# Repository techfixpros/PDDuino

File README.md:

# PDDuino
A [Tandy Portable Disk Drive](http://tandy.wiki/TPDD) emultaor implemented on Arduino, using a micro-sd card for storage.

<!-- old gmail acct

-->

<!--
Earlier stages:<br>

-->

PDDuino was based originally on [SD2TPDD](https://github.com/tangentdelta/SD2TPDD) by Jimmy Petit.  

DISCLAIMER: This is not a great reference for a TPDD server yet. [dl2](https://github.com/bkw777/dl2) is.  
[pdd.sh](https://github.com/bkw777/pdd.sh) is a good reference for a TPDD _client_, though not especially easy to follow the bash code since it is written to conform to a purist standard as a stunt more than to be easy to read and follow.  
The next major TODO is to rewrite this using dl2 as the reference.

## Features
* Tandy Portable Disk Drive 1 emulation
* TS-DOS directories<br>
* TPDD2-style bootstrapper to install a [TPDD Client](http://tandy.wiki/TPDD_client) onto the computer<br>

## Hardware support
PDDuino runs on most any Arduino-compatible microcontroller.  

Configs are already included to support the following particularly handy development boards that have a small form factor, built-in usb power & console, and built-in SD-card reader, and which are supported by [MounT](https://github.com/bkw777/MounT) and [BCR_Breakout](https://github.com/bkw777/BCR_Breakout) for the serial connection, power, and physical attachment to the computer.  
 * Teensy [3.5](https://www.pjrc.com/store/teensy35.html) and [3.6](https://www.pjrc.com/store/teensy36.html)  ([4.1](https://www.pjrc.com/store/teensy41.html) pending)  
 * Adafruit [Feather 32u4 Adalogger](https://www.adafruit.com/product/2795)(most recommended) and [Feather M0 Adalogger](https://www.adafruit.com/product/2796)

PDDuino may be used with any machine that has [TPDD client](http://tandy.wiki/TPDD_client) software or firmware.  
 * TRS-80/TANDY Models 100, 102, 200, WP-2  
 * NEC PC-8201, PC-8201A, PC-8300, PC-8401A, PC-8500  
 * Olivetti M10  
 * Kyotronic KC-85  
 * [Cambridge Z88](http://www.rakewell.com/xob/xob.shtml)  
 * [Brother knitting machines](http://www.k2g2.org/wiki:brother_fb-100)  
 * [Anything with a python interpreter](https://trs80stuff.net/tpdd/)  
 * [pdd.sh](https://github.com/bkw777/pdd.sh)  

## Requirements / Setup
### Software
[Arduino IDE Setup](Arduino_IDE_Setup.txt)

### Hardware
* Arduino-compatible microcontroller board with at least one hardware serial port
* SD card reader
* RS-232 to TTL/CMOS level shifter
* Serial cable
* Battery or usb power source for the microcontroller board

These boards have a small form-factor, and sd-card reader built-in:  
  [Adafruit Feather 32u4 Adalogger](https://learn.adafruit.com/adafruit-feather-32u4-adalogger) (best choice)<br>
  [Adafruit Feather M0 Adalogger](https://learn.adafruit.com/adafruit-feather-m0-adalogger) (20200916 broken)<br>
  [Teensy 3.5](https://www.pjrc.com/store/teensy35.html)<br>
  [Teensy 3.6](https://www.pjrc.com/store/teensy36.html)<br>
  [Teensy 4.1](https://www.pjrc.com/store/teensy41.html) (not yet tested)

  The ideal is the Alalogger 32u4, even though it's old and you can get far more powerful boards for the same or less cost, and you may have to get it from a reseller like Digikey or Mouser, the Adalogger 32u4 is really the optimal choice for several reasons, at least until the glitch with the M0 version is worked out, or one of the new Huzzah boards are supported.

  The Teensy's work well in all the impoprtant ways, but they have symmetrical pin headers so they can be plugged in backwards, don't have battery connectors or chargers, or card-detect switches on the card slots. The extra led next to the card slot on the Adafruit boards is nice for a disk activity light too. But without wifi and with the ability to underclock down to nothing, they draw low enough power that the lack of battery is offset by the fact that it can be powered from the BCR port without destabilizing the computer.

This adapter takes the place of a serial cable, and includes the level-shifter:<br>
  [MounT](https://github.com/bkw777/MounT)

This adapter can power the microcontroller board from the M100:<br>
  [BCR-USB-Power adapter](http://www.github.com/bkw777/BCR_Breakout)

**The following below are NOT needed if using the MounT adapter.  
You would only need these for bread-boarding or building in a box attached by a cable.**

 RS-232&lt;--&gt;TTL/CMOS level-shifter module:  
  [NulSom](https://www.amazon.com/dp/B00OPU2QJ4/)  
  Has a male connector and DTE pinout like a PC  
  Use the same special null-modem cable as for connecting a "Model T" to a PC.  
  Solder jumper wires on the back of the 9-pin connector to join pins 1, 4, and 6  
  [DSR-DTR-DCD Wiring, top](https://photos.app.goo.gl/oBpAbAbCgE8yCJzm7)  
  [DSR-DTR-DCD Wiring, bottom](https://photos.app.goo.gl/mj1SXce5fJnmZiyr6)  
  This short-circuits the DSR/DTR detection, which pacifies TS-DOS so it will run, but means you can't test the bootstrap function except by wiring up a fake DTR/DSR signal using a pulldown resistor to gnd and a momentary button to vcc/3v3 on gpio pin 6.  

 RS-232 cable:  
  [PCCables 0103](https://www.pccables.com/products/00103.html)  
  Or [Any of these](http://tandy.wiki/Model_T_Serial_Cable)

 TODO: find a ttl-serial module that actually supports the dsr/dtr lines.  
  https://www.pololu.com/product/126   breadboard-friendly single row of pins  
  https://www.amazon.com/dp/B0190WSINY/  double row pin header needs jumper wires to a breadboard  
  Female plug, DCE pinout, needs a different serial cable, or adapters.

## Usage:
### Normal usage
Use as you would use a real [TPDD](http://tandy.wiki/TPDD) or any other [TPDD emulator](http://tandy.wiki/TPDD_Emulators).

### Bootstrap Procedure
Assuming you are using a [MounT](https://github.com/bkw777/MounT) adapter to host a Feather or Teensy.  
Assuming you are using the [BCR-USB](https://github.com/bkw777/BCR_Breakout) adapter to power the MounT.  
Assuming the portable is a Model 100.  
Assuming you want to install TS-DOS.  

1. Start with the Model 100 turned off.  
 Plug the MounT and BCR adapters into the Model 100 and connect the usb cable from the BCR adapter to the MounT.  
 Eject the SD card.

1. Place an ascii format BASIC loader file on the root of the SD card, renamed as LOADER.DO.  
You can use any of the loader files from [dlplus](https://github.com/bkw777/dlplus/tree/master/clients).  
&nbsp;  
Example 1: To install TS-DOS on a TRS-80 Model 100: Take [TS-DOS.100](https://raw.githubusercontent.com/bkw777/dlplus/master/clients/ts-dos/TS-DOS.100), and save it as ```LOADER.DO``` on the root of the SD card.  
Note the associated [pre-install](https://raw.githubusercontent.com/bkw777/dlplus/master/clients/ts-dos/TS-DOS.100.pre-install.txt) and [post-install](https://raw.githubusercontent.com/bkw777/dlplus/master/clients/ts-dos/TS-DOS.100.post-install.txt) directions.  
&nbsp;  
Example 2: To install DSKMGR on an Olivetti M10: Take [DSKMGR.M10](https://raw.githubusercontent.com/bkw777/dlplus/master/clients/dskmgr/DSKMGR.M10), and save it as ```LOADER.DO``` on the root of the SD card.  
Note the associated [pre-install](https://raw.githubusercontent.com/bkw777/dlplus/master/clients/dskmgr/DSKMGR.M10.pre-install.txt) and [post-install](https://raw.githubusercontent.com/bkw777/dlplus/master/clients/dskmgr/DSKMGR.M10.post-install.txt) directions.  

1. Turn on the Model 100 while the SD card is still ejected.  
The Arduino board should now have a steady slow blinking LED, indicating it's waiting for an SD card.  
Don't insert the SD card yet.

1. In BASIC, type ```RUN "COM:98N1E"``` and press Enter.  
(Or follow the pre-install directions are for the loader you're using. The exact command is different for different models of computer. This example is for TRS-80 Model 100 or 102.)

1. Insert the SD card.

1. Wait while the loader program is transferred and then executed.  
For approximately 20 seconds (exact time depends on the size of LOADER.DO) there will be no indication of acivity on the computer, and the LED on the Arduino board will be ON solid and not blinking. The loader program is being sent to the computer during this time.  
&nbsp;  
After the LED goes out, the computer executes the program that was just loaded.  
&nbsp;  
Follow any on-screen directions (different loaders have different prompts & directions), and the post-install directions for the loader you're using.  
In the case if TS-DOS, this would be:  
&nbsp;&nbsp;Type ```SAVE "TS-DOS"``` and press Enter.  
&nbsp;&nbsp;Exit BASIC (press ```F8``` or type ```MENU```)  
&nbsp;&nbsp;Run ```TS-DOS.BA``` from the main menu.  
&nbsp;&nbsp;Use ```F2-Kill``` to delete ```TMP.DO```  

You now have the ram version of TS-DOS (or other tpdd client) installed.  
You can immediately use it to browse the contents of the SD card.

## Notes
### Ultimate ROM II TS-DOS loader
If you plan on using Ultimate Rom II, it has a "TS-DOS" feature which works by loading TS-DOS into ram on the fly, from a file on disk.  
The file must be named DOS100.CO, and be in the root directory of the media.  
This file can be downloaded from <http://www.club100.org/nads/dos100.co>, or,  
a modified/updated version can be found here: <http://www.club100.org/memfiles/index.php?direction=0&order=&directory=Ken%20Pettit/NewDos>

### "Model T" serial port control lines
At power-on the Model 100 rs232 port sets all data & control pins to -5v.  
On RUN "COM:98N1E", pins 4 and 20 go to +5v.  

## To-Dos, or merely ideas, not necessarily realistic
* Change "PARENT.<>" to "..<>" if possible
* https://www.arduinolibraries.info/libraries/double-reset-detector_generic
* https://github.com/rocketscream/Low-Power  
  simplify the sleep calls, same lib for both avr and samd21  
* RTC (Teensy has built-in rtc)
* play & record audio as virtual cassette (Teensy has built-in audio, and enough cpu & ram to use it)
* Battery level (Adalogger has built-in voltage reference and adc, and a built-in lipo charger)
* A command-line that can be accessed from the computer's terminal emulator for quicker file manipulation
* Hayes modem emulation using an ESP8266 (<https://www.cbmstuff.com/proddetail.php?prod=WiModem232>)
* FTP server/client access using an ESP8266

## BUGS/STATUS
* 20200916 Feather M0 isn't working.  
  Unknown why. It used to work.

* Works with TS-DOS.

* Doesn't work with TEENY. (hangs)

* File transfers don't work with TpddTool.py .  
Seems to be due to mis-matches in handling the space-padding in the filenames?  
Problem may be at least partly in TpddTool.py

* Some kind of working directory initial/default state issue, which affects Ultimate Rom II loading DOS100.CO on the fly.
If you have DOS100.CO in ram, then UR-2 works all the time, because it will use that copy if available.  
TS-DOS from rom or ram, not via UR-2, seems to be working pretty well all the time.  
TS-DOS from rom or ram, not via UR-2, can successfully load a file like DOS100.CO from the root dir, but Ultimate Rom 2 usually can not load that same file, but sometimes it can.  
If you try to use TS-DOS from UR2 after a fresh power-cycle of both Arduino and M100, It doesn't work.  
But If you load TS-DOS some other way (for example, use a REX to switch to TS-DOS rom), and use TS-DOS to read the directory listing once, then switch roms back to UR-2, THEN the TS-DOS menu entry in UR-2 works (successfully loads DOS100.CO from the disk).  
Maybe TS-DOS does some kind of initialization that UR-2 isn't doing?  
UR-2 works fine with a real TPDD/TPDD2 and other emulators like dlplus and LaddieAlpha, so maybe there is some sort of default condition that we should be resetting to?  

* If you use UR-2 to load TS-DOS in ram, and switch to a subdirectory like /Games while in TS-DOS, then exit TS-DOS, then you can't use TS-DOS any more, because the next time UR-2 tries to load DOS100.CO from disk, SD2TPDD looks for /Games/DOS100.CO, which does not exist.

* When UR-2 loads DOS100.CO, sucessfully or not, the LED doesn't shut off after.

* Sometimes displays the "PARENT.<>" directory entry even when you are already in the root dir.  
Goes away if you try to open PARENT.<> again when you're already in root.

## Change-log

### 20210404
* 0.5.0 Incorporated Jim Brain's replacement return_*() and main loop.

### 20200819
* Moved PCB to its own [repo](https://github.com/bkw777/MounT)  
* Added TPDD2-style bootstrap function  

### 20200817
* Added PCB adapter "PDDuino_Feather".  
 Takes the place of the serial cable and ttl-rs232 module.  
 Supports Adafruit Feather 32u4 Adalogger and Adafruit Feather M0 Adalogger.  

### 20191025
* Support Adafruit Feather M0 Adalogger  
 needs "compiler.cpp.extra_flags=-fpermissive" in ~/.arduino15/packages/adafruit/hardware/samd/1.5.4/platform.local.txt
* Combine all boards supported into the same code  
 Time to break this out into a config.h file?

### 20180921
* Support Teensy 3.5/3.6
* Support Adafruit Feather 32u4 Adalogger
* Macro-ify all serial port access, debug and tpdd client
* sleepNow() powersaving, idles at 3ma
* dmeLabel[] & setLabel() TS-DOS shows current working dir in top-right corner
* disk-activity led

### SD2TPDD - PDDuino

### v0.2 (7/27/2018)
* Added DME support
* Corrected some file name padding bugs

### v0.1 (7/21/2018)
* Initial testing release with basic TPDD1 emulation

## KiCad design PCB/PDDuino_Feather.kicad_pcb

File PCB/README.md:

# PDDuino PCBs

## PDDuino_Feather - for Adafruit Feather Adalogger, 32u4 and M0

Get the PCB from OSHPark: <https://oshpark.com/shared_projects/0NVCii0o><br>
Get the parts from Digi-Key: <https://www.digikey.com/short/zr423m><br>

The Digi-Key cart is a complete BOM, including Feather 32u4 Adalogger board, 105mah lipo battery, and pin header sockets.<br>

You may want to remove any/all the following from the cart:<br>
* Battery - If you use the BCR port or other usb power source, then you don't need the battery.<br>
* Socket headers - If you want to solder the Adalogger board, then you don't need the sockets.<br>
* Adalogger board - If you already have one, you don't necessarily need more.

The same PDDuino_Feather adapter board works for both the 32u4 and the M0 versions of Adalogger boards.

## PDDuino_Teensy35 - for Teensy 3.5
coming

## PDDuino_Teensy36 - for Teensy 3.6
coming

## PDDuino_Teensy41 - for Teensy 4.1
coming

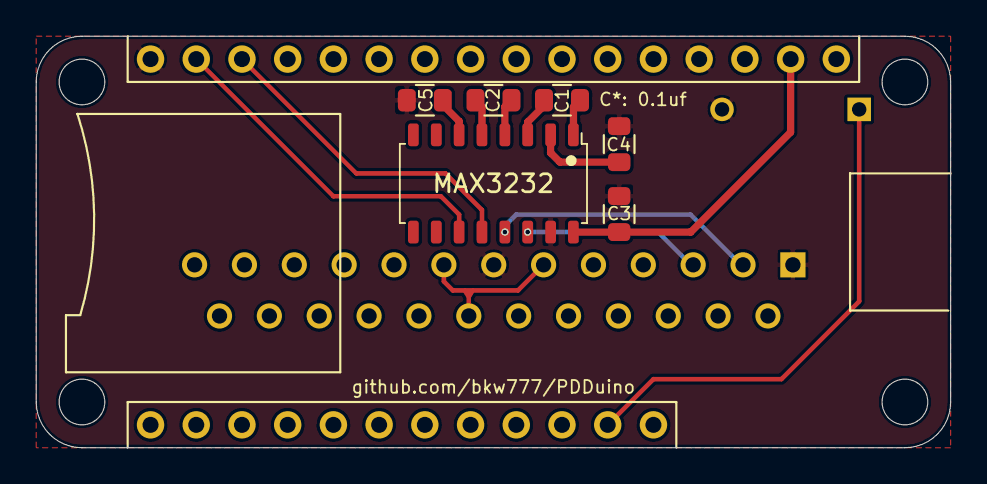
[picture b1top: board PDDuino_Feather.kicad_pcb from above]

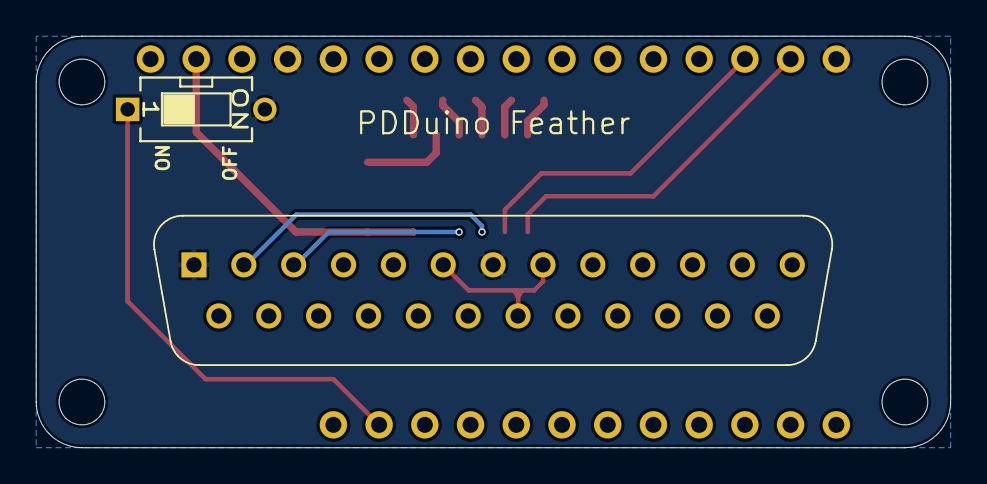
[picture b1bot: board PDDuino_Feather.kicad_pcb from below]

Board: 2 copper layers, 50.8 x 22.9 mm, 10 parts (2 on the bottom side), 16 nets.

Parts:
C1, C2, C3, C4, C5: 0.1uf; C_0805
J1: Adafruit_Feather_Adalogger
J2: DB25_Male; DSUB-25_Male_Vertical_P2.77x2.84mm
NT1: Net-Tie_3_Tee; NetTie-3_SMD_10_tri
S1: DS04-254-1L-01BK; SW_DS04-254-1L-01BK
U1: MAX3232; SOIC-16_W3.90mm

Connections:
/3V3: C3.1, J1.2, U1.16
/DCD: J2.8, NT1.1
/DSR: J2.6, NT1.3
/DTR: J2.20, NT1.2
/En: J1.27, S1.1A
/RXD: J2.3, U1.14
/RXD_TTL: J1.14, U1.12
/TXD: J2.2, U1.13
/TXD_TTL: J1.15, U1.11
GND: C3.2, C4.2, C5.2, J1.4, J1.16, J2.1, J2.7, S1.1B, U1.15
unnamed: C1.1, U1.1
unnamed: C1.2, U1.3
unnamed: C2.1, U1.4
unnamed: C2.2, U1.5
unnamed: C4.1, U1.2
unnamed: C5.1, U1.6

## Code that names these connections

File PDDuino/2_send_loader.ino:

#if defined(LOADER_FILE)
/*
 * sendLoader() and restart()
 *
 * At power-on the Model 100 rs232 port sets all data & control pins to -5v.
 * On RUN "COM:98N1E", pins 4 (RTS) and 20 (DTR) go to +5v.
 * github.com/bkw777/MounT connects GPIO pin 5 through MAX3232 to RS232 DSR (DB25 pin 6) and to RS232 DCD (DB25 pin 8)
 * and connects RS232 DTR (DB25 pin 20) through MAX3232 to GPIO pin 6.
 * To assert DTR (to RS232 DSR), raise or lower GPIO pin 5.
 * To read DSR (from RS232 DTR), read GPIO pin 6.
 */

/* TPDD2-style bootstrap */
void sendLoader() {
  byte b = 0x00;
#if DEBUG
  int c = 0;
#endif // DEBUG
  File f = SD.open(LOADER_FILE);

  DEBUG_PRINTL(F("sendLoader()"));  
  if (f) {
    SD_LED_ON
    DEBUG_PRINT(F("Sending " LOADER_FILE " "));
      while (f.available()) {
        b = f.read();
        CLIENT.write(b);
#if DEBUG
        if(++c>99) {
         DEBUG_PRINT(F("."));
         c = 0;
        }
#endif // DEBUG
        delay(LOADER_MS_PER_BYTE);
      }
    f.close();
    SD_LED_OFF
    CLIENT.flush();
    CLIENT.write(BASIC_EOF);
#if defined(BOARD_FEATHERM0)    // some kind of bug with M0
    delay(250);                 // need to send the 0x1A twice, and need to delay between them
    CLIENT.write(BASIC_EOF);    // 2 in a row doesn't work, delay alone before sending 1 doesn't work
#endif // BOARD_FEATHERM0
    CLIENT.flush();
    CLIENT.end();
    DEBUG_PRINTL(F("DONE"));
  } else {
    DEBUG_PRINT(F("Could not find " LOADER_FILE " ..."));
  }
  restart; // go back to normal TPDD emulation mode
}
#endif // LOADER_FILE

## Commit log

2018-09-18 bkw changes for Adalogger 32u4, DEBUG_PRINT*, cardInit(), sleepNow(), SD_LED_*, setLabel()/dmeLabel[], CLIENT.*
2018-09-22 dmeLabel, and reduce ram consumption
2019-10-25 combine different board supports in one branch
2019-10-25 get all supported boards working in the same code
2019-10-25 update docs a little
2019-10-26 get M0 sleep() working, or at least building
2020-07-31 Add video of Adafruit 32u4 powered from BCR
2020-08-01 rename project
2020-08-17 Add PDDuino_Feather PCB
2020-08-17 typo in readme
2020-08-17 fix OSHPark rendering glitch, top solid white silkscreen
2020-08-17 update digikey cart, add power switch
2020-08-17 oshpark link
2020-08-19 Move PCB to own repo, add TPDD2-style bootstrap
2020-08-19 describe bootstrap operation
2020-08-19 comments
2020-08-20 video of new bootstrapper
2020-08-26 fix inverted logic for DSR & DTR
2020-08-28 readme
2020-08-31 readme, about bootstrap procedure
2020-09-09 fix M0 compiler errors
2020-09-13 pullup DSR
2020-09-14 detect platform from IDE, un-hardcode CLIENT & CONSOLE & LED_BUILTIN, more debug output
2020-09-15 Work-around Adafruit broke their SAMD21 support github.com/adafruit/ArduinoCore-samd/issues/209
2020-09-16 Add card-detect support to reset on eject. docs & notes
2020-09-17 break into multiple files
2020-09-17 file split broke debug, function needs a prototype now
2020-09-17 debug strings and debug sleep level
2020-09-17 debugging & comments
2020-09-22 improve docs, details, many links
2020-09-23 fix link to dlplus clients
2021-04-04 0.4.2 - Jim Brain's refactored return_*(). Replace magic numbers with #defines
2021-04-04 Jim Brain's main loop
2021-04-05 finally fixed setLabel()
2021-04-05 setLabel()
2021-09-22 don't use FILE_WRITE as it includes O_APPEND
2022-08-24 increase per-byte sleep in sendLoader()
2022-08-27 fix F_OPEN_WRITE missing O_CREAT
